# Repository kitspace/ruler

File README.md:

# Kitspace PCB Ruler

A PCB design reference ruler made using Inkscape, [svg2shenzhen](https://github.com/badgeek/svg2shenzhen/) and KiCad (v5). It's up [on Kitspace](https://kitspace.org/boards/github.com/monostable/ruler/) of course. You can [buy it on Tindie](https://www.tindie.com/products/kasbah/kitspace-pcb-ruler-2/) while stocks last.

- You can use it as a ruler and as a reference for footprint sizes when working on a PCB design.
- The front is a functioning circuit if you populate it. The LEDs will light up if you connect it via USB and press the buttons.
- There are also pads for testing LED polarity.
- It's in a panel to show off two different ways to attach designs within a panel: mouse-bites and v-score. These are indicated on the back as well.

<iframe width="560" height="315" src="https://www.youtube.com/embed/yOuZpUTyYj4" frameborder="0" allow="accelerometer; autoplay; encrypted-media; gyroscope; picture-in-picture" allowfullscreen></iframe>

## License

<br />This work is licensed under a <a rel="license" href="http://creativecommons.org/licenses/by-sa/4.0/">Creative Commons Attribution-ShareAlike 4.0 International License</a>.

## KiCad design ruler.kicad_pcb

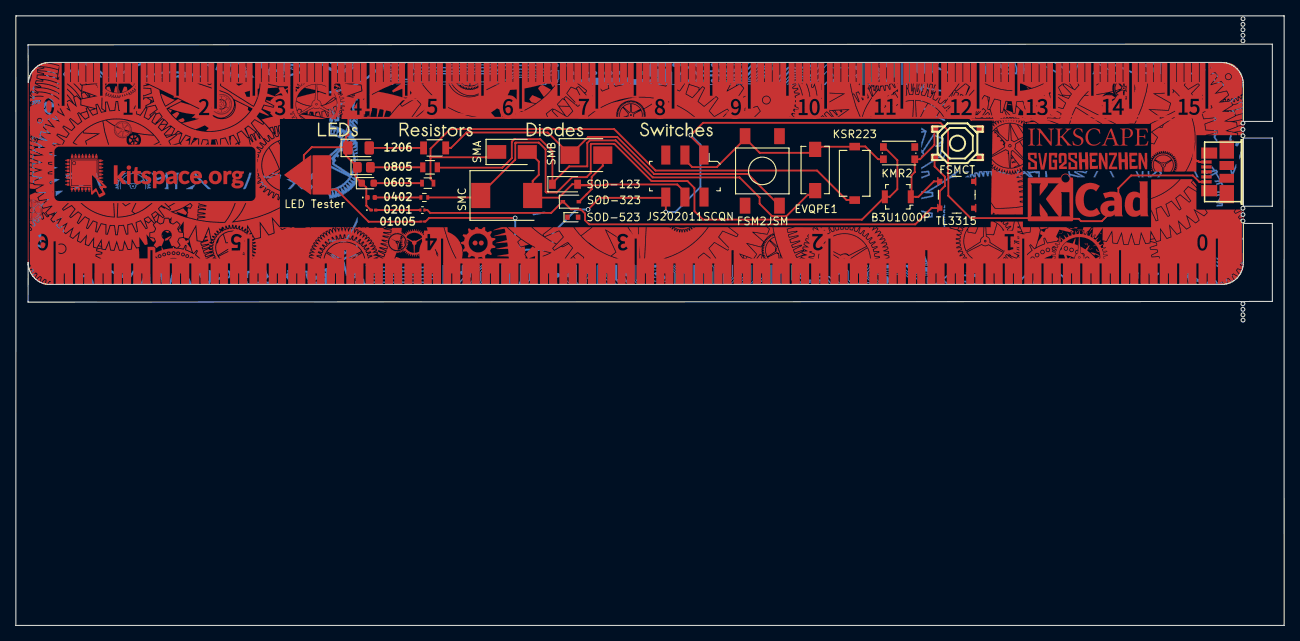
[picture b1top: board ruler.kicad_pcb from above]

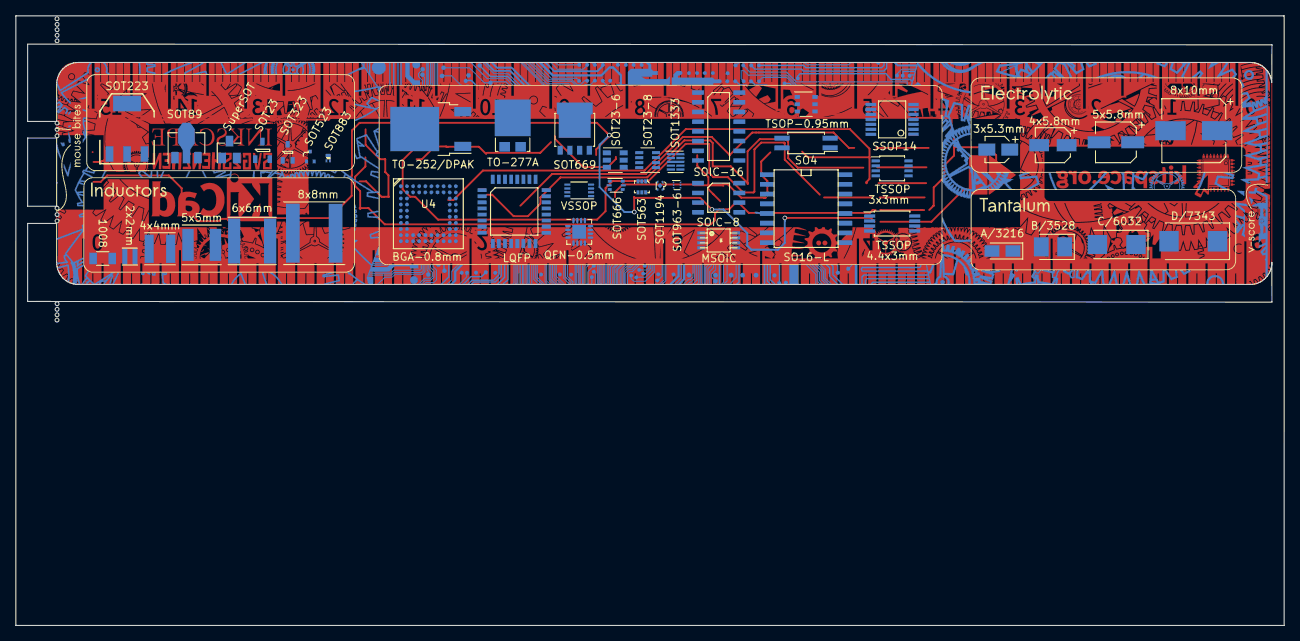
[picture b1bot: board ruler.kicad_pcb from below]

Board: 2 copper layers, 166.0 x 79.8 mm, 79 parts (47 on the bottom side), 15 nets.

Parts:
C1: 3x5.3mm; CP_Elec_3x5.3
C2: 4x5.8mm; CP_Elec_4x5.8
C3: 5x5.8mm; CP_Elec_5x5.8
C4: 8x10mm; CP_Elec_8x10
C5: A/3216; CP_Tantalum_Case-A_EIA-3216-18_Reflow
C6: B/3528; CP_Tantalum_Case-B_EIA-3528-21_Reflow
C7: C/6032; CP_Tantalum_Case-C_EIA-6032-28_Reflow
C8: D/7343; CP_Tantalum_Case-D_EIA-7343-31_Reflow
D1: SMA; D_SMA
D2: SMB; D_SMB
D3: SMC; D_SMC
D4: SOD-123; D_SOD-123
D5: SOD-323; D_SOD-323
D6: SOD-523; D_SOD-523
DRAWING1: Conn_01x01; ruler
DRAWING2: Conn_01x01; leds_text
DRAWING3: Conn_01x01; resistors_text
DRAWING4: Conn_01x01; diodes_text
DRAWING5: Conn_01x01; switches_text
DRAWING9: Conn_01x01; inductors_text
DRAWING10: Conn_01x01; tantalum_text
DRAWING11: Conn_01x01; electrolytic_text
J1: USB_OTG; conn_usb_B_micro_smd
L1: 1008; Inductor_1008
L2: 8x8mm; Inductor_Taiyo-Yuden_NR-80xx
L3: 4x4mm; Inductor_Taiyo-Yuden_MD-4040
L4: 5x5mm; Inductor_Taiyo-Yuden_MD-5050
L5: 6x6mm; Inductor_Taiyo-Yuden_NR-60xx
L6: 2x2mm; Inductor_Taiyo-Yuden_NR-20xx
LED1: LED Tester; led_test_pads
LED2: 0402; LED_0402_1005Metric
LED3: 0603; LED_0603_1608Metric
LED4: 0805; LED_0805_2012Metric
LED5: 1206; LED_1206_3216Metric
LED6: 0201; LED_0201_0603Metric
Q1: SOT23; SOT-23
Q2: SOT323; SOT-323
Q3: SOT883; SOT-883-B
Q4: SOT523; SOT-523
Q5: SOT223; SOT223_GND_VO_VI
Q6: SOT89; SOT-89-3
Q7: SuperSOT; SuperSOT-3
R1: 1k; R_0201
R2: 1k; R_0402
R3: 1k; R_0603
R4: 1k; R_0805
R5: 1k; R_1206
R6: 1k; R_01005_0402Metric
SW1: KMR2; SW_SPST_KMR2
SW2: EVQPE1; SW_SPST_EVQPE1
SW3: B3U1000P; Switch_Tactile_SMD_B3U-1000P
SW4: FSMCT
SW5: TL3315; Switch_4.5x4.5mm_SMD_TL3315NF160Q
SW6: FSM2JSM; FSM2JSMA
SW7: JS202011SCQN; Switch_Slide_JS202011SCQN
SW8: KSR223; KSR
U1: QFN-0.5mm; QFN-16-1EP_3x3mm_Pitch0.5mm
U2: LQFP; LQFP-32
U3: SOIC-8
U4: BGA-0.8mm; BGA-64-0.8mm
U5: TSSOP; TSSOP-8_3x3mm_Pitch0.65mm
U6: MSOIC; msoic-8
U7: TSOP-0.95mm; TSOP-6_1.65x3.05mm_Pitch0.95mm
U8: SOT23-6; SOT-23-6
U9: SOT23-8; SOT-23-8
U10: SOT963-6; SOT-963
U11: SSOP14; SSOP-14
U12: SO16-L; SO-16-L
U13: SOT666; SOT-666
U14: SOT1194; SOT-1194-1
U15: SOT1333; SOT-1333-1
U16: SOT669; SOT-669_LFPAK
U17: TSSOP; TSSOP-8_4.4x3mm_Pitch0.65mm
U18: SO4; SO-4_4.4x2.3mm_Pitch1.27mm
U19: VSSOP; VSSOP-8_2.3x2mm_Pitch0.5mm
U20: TO-252/DPAK; TO-252-2
U21: TO-277A
U22: SOIC-16
U23: SOT563; SOT-563

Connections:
+5V: J1.1, R6.1, SW7.1, SW7.6
GND: J1.5, LED1.1, LED2.1, LED3.1, LED4.1, LED5.1, LED6.1
LED_V+: D1.2, D2.2, D3.2, D4.2, D5.2, SW7.5
unnamed: D1.1, R3.1, SW8.2
unnamed: D2.1, R5.1, SW6.2
unnamed: D3.1, R2.1, SW1.2, SW3.2
unnamed: D4.1, R4.1, SW2.2
unnamed: D5.1, R1.1, SW4.1, SW4.2, SW5.1, SW5.2
unnamed: LED1.2, R6.2
unnamed: LED2.2, R2.2
unnamed: LED3.2, R3.2
unnamed: LED4.2, R4.2
unnamed: LED5.2, R5.2
unnamed: LED6.2, R1.2
SW_V+: SW1.1, SW2.1, SW3.1, SW4.3, SW4.4, SW5.3, SW5.4, SW6.1, SW7.2, SW8.1

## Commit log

2018-04-12 Extend ruler, use rounded edges, sort out numbers
2018-04-12 Add url and logo
2018-04-13 Adjust logo
2018-04-13 Move inches to front bottom
2018-04-13 Experiment with slikscreen logo
2018-04-13 More silkscreen, switch to svg2shenzhen dev vers.
2018-04-19 Adjust stuff
2018-04-19 Switch to using kicad_mod for pcb art
2018-04-28 Add some drills in drawing
2018-04-28 Add animal footprints
2018-04-29 Add cat footprint and copper to bottom seperators
2018-05-04 Add surrounding frame
2018-05-08 Sort out mouse-bite silkscreen
2018-05-08 Adjust logo and copper spacing from v-score
2018-05-08 Clear out old stuff, include drawing as module
2018-05-08 Add some push-buttons and LEDs to schematic
2018-05-08 Do some layouting
2018-05-08 Add more push-buttons
2018-05-08 Re-enable switching individual LEDs on
2018-05-08 Add bigger resistors
2018-05-08 Add diodes
2018-05-09 Add copper behind kitspace logo in drawing
2018-05-09 Adjust mouse-bites to accommodate USB connector
2018-05-09 Re-arrange push-button connections
2018-05-09 Re-arrange and replace some switches
2018-05-09 Adjust led test pads
2018-05-09 Route route route
2018-05-09 Tweak routing
2018-05-09 Add 1/20 inch markers
2018-05-09 Add inductors, caps, transitors and ICs
2018-05-09 Change text to inkscape versions
2018-05-09 Adjust title texts
2018-05-09 Add more text
2018-05-09 Adjust led tester text
2018-05-09 Add more ICs
2018-05-09 Re-arrange footprints
2018-05-10 Add drawings, ants etc
2018-05-10 Adjust logos
2018-05-10 More logo adjustements
2018-05-10 Adjust inductors
2018-05-20 A lot of changes
2018-05-20 Adjust mouse-bite drills and plot
2018-05-21 Adjust bottom separator graphics
2018-05-21 Panelize two rulers
2018-05-21 Make adjustements for AllPCB panelization
2018-05-21 Update svgs
2018-06-28 Add readme
2018-06-29 Add 1-click BOM
2018-06-29 Add description and screenshots
2018-06-29 Add kitspace.yaml
2018-06-29 Add comment about issues
2018-06-29 Add Kitspace link
2018-06-30 Remove second copy for now, remove all tracks
2018-06-30 Add license
2018-06-30 Add KiCad version info
2018-07-13 Make ant better
2018-07-13 Give back Cu a nice background
2018-07-13 Sort out usb pads and connections
2018-07-13 Use gears as background for the logos
2018-07-13 Work on back layout and graphics
2018-07-26 Make left gears more copper full
2018-07-26 More gears!
2018-07-26 Give cm numbers and lines some surrounding copper
2018-07-26 Put copper around inch numbers and marks
2018-07-26 Gears me dears
2018-07-26 Add fosdem and oshw logos
2018-07-27 Adjust gears
2018-08-12 Re-save schematic with kicad 4
2018-08-12 Add another switch
2018-08-12 Convert to kicad-5 properly?
2018-08-12 Add a tactile switch and 0201 LED
2018-08-12 Route
2018-08-12 Move some stuff around and plot
2018-08-13 Move stuff around
2018-08-13 Fix power track
2018-08-13 Fix text line width for a sot
2018-08-13 Move gears
2018-08-13 Flip the inch markers
    fixes #15
2018-08-13 Add a v-score between rulers
    fixes #12
2018-08-13 Make v-score pointer line thinner
2018-08-13 Adjust tracks
2018-08-13 Switch out second b3u button
2018-08-13 Add some drills, remove some drawings
2018-08-13 Duplicate the layout into the frame
2018-08-14 Update BOM
2018-08-14 Adjust b3u button text
2018-08-14 Improve part selection for mouser
2018-08-16 Remove trace crossing 4 on the ruler marks
2018-08-16 Re-arrange buttons
2018-08-16 Route buttons, clean up
2018-08-16 Adjust traces a bit
2018-08-16 Adjust component bubbles
2018-08-16 Add more footprints on back
2018-08-16 More footprints on back
2018-08-16 Use newer kicad LED footprints, adjust buttons
2018-08-16 Clean up tracks a bit
2018-08-16 Add 0s to ruler markings
2018-08-16 Align some footprints
2018-08-16 Duplicate circuit and adjust placement
2018-08-16 Increase text size for v-score and mouse-bites
2018-08-17 Reduce inkscape export dpi to 1000
2018-08-20 Increase line thickness and reduce DPI
2018-10-21 Update pictures
2018-10-21 Remove note about issues in readme
2018-11-01 Add pics without panel
2018-11-18 Add populated pic and video
2018-11-19 Add tindie link
2018-12-06 Fix SMC diode selection in BOM
2019-12-17 Remove gerbers for kitspace test
2020-12-10 Fix upside down 6
2020-12-11 Add kicad file to kitspace.yaml
2023-03-29 Fix fonts
2023-03-29 Switch kitspace color to black
2024-05-24 Add gerbers
2024-05-24 Update design to de-clutter bottom side
2024-05-24 Add 1/10 inch marker
2024-05-25 Increase v-score rail width
